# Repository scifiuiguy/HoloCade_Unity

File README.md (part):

# HoloCade for Unity

**HoloCade SDK** - A comprehensive SDK for developing VR/AR Location-Based Entertainment experiences in Unity with support for AI facial animation, large hydraulic haptics, and embedded systems integration.

<details>
<summary><strong>⚠️Author Disclaimer:</strong></summary>

<blockquote>
This is a brand new plugin as of November 2025. Parts of it are not fully fleshed out. The author built location-based entertainment activations for Fortune 10 brands over the past decade. This is the dream toolchain he wishes we had back then, but it probably still contains unforeseen bugs in its current form. V1.0 is considered Alpha. If you're seeing this message, it's because HoloCade has yet to deploy on a single professional project. Please use this code at your own risk. Also, this plugin provides code that may or may not run on systems your local and state officials may classify as  "amusement rides" or "theme park rides" which may fall under ASTM standards or other local regulations. HoloCade's author disclaims any liability for safety of guests or patrons or regulatory readiness. Please review the local regulations in your area prior to executing this code in any public venue. You are responsible for compliance in your state.
</blockquote>

</details><br>

> **🔗 Unreal Version:** Also available at [github.com/scifiuiguy/holocade_unreal](https://github.com/scifiuiguy/holocade_unreal)

---

## 📖 Overview

HoloCade is a comprehensive SDK for developing VR and AR Location-Based Entertainment (LBE) experiences. This repository **is** the **Unity 6 LTS** HoloCade package (`package.json` at the root), intended for use inside Unity projects via Package Manager or by embedding under `Packages/com.ajcampbell.holocade/`.

The HoloCade SDK democratizes LBE development by providing:
- **Experience Genre Templates** - Drag-and-drop complete LBE solutions
- **Low-Level APIs** - Technical modules for custom integration between game engine and various physical systems
- **AI-Driven Facial Animation** for immersive theater live actors (automated w/ NVIDIA ACE)
- **Wireless Trigger Controls** - Embedded buttons in costume/clothing for narrative state machine control through WiFi/Bluetooth
- **Large-Scale Hydraulic Haptics** for lift/motion platforms
- **Embedded Systems Integration** for costume-/prop-/wall-/furniture-mounted interfaces
- **Embedded Sensors** temperature, motion, face, and body tracking sensors to trigger escape room actions
- **Co-located XR Multiplayer LAN Experiences** with Unity NetCode for GameObjects
- **HMD and Hand Tracking** via OpenXR (Unity's native XR system)
- **6DOF Tracking** with SteamVR trackers and future extensibility

<details>
<summary><strong>⚠️OpenXR Note:</strong></summary>

<blockquote>
HoloCade uses **OpenXR exclusively** for all HMD and hand tracking access through Unity's native XR system (`XRHandSubsystem`, `InputDevices`). If OpenXR is not desired for your LBE deployment for any reason, but you still want to use an HoloCade experience genre template to get started, there may be some customization necessary in `HoloCadeHandGestureRecognizer` and in some of the Experience classes. Anywhere OpenXR is referenced, you may need to create an alternative version of that class with your SDK of choice replacing OpenXR usage.

</blockquote>

</details><br>

---

## 💭 Philosophy

<details>
<summary><strong>Why HoloCade?</strong></summary>

<blockquote>

Home console VR usage is nascent and difficult despite being steadily on the rise:
* 80 million monthly active users in the U.S. in 2025
* up 60% from 2020
* 10% of Americans started using VR regularly so far this decade

If that growth holds, we might reach 100 million regular VR users by end-of-decade, more than 1/4 of the population. It's not smartphone-era growth, but it's steady.

BUT...

Content budgets are skin-and-bone. 

Building for VR requires specialty talent compared to film/TV/gaming, and every dollar spent goes half as far due to...
* deeper fidelity challenges
* bigger QA hurdles
* evil perf op constraints

VR devs need a leg up. The industry has been in a funding desert since the Pandemic. "VR is all hype" rumors put the dev community on a respirator, and we never got off the ropes.

I get where investors are coming from. We're 10 years into modern VR. They need proof of ROI. We need to deliver in the black. We need better tools. We were building cars without factories.

A better analogy - Movie Theaters:
If a Hollywood studio invested millions on a new film before the streaming era, they'd be sunk if there were no 35mm projector and no movie theaters hungry to roll the next hit.

An even better analogy - the JAMMA Arcade Spec:
In 1985, the arcade industry was in a slump. All the arcade boxes were proprietary. Venues had to buy a new arcade box for every game. Devs had to design a whole arcade box for just THEIR game. Enter the JAMMA Spec. Suddenly venues could leave the same box in place and swap a card, and suddenly it's a new game! Same hardware, fresh regular content. Devs could focus on the game knowing reliable hardware was already on-site.

We need that for the VR industry:
* Devs need to be able to focus on dev, not hardware
* Venues need standard hardware so devs can bring them regular new content.

We have an chicken-egg situation. A standard spec for VR LBE is what we need.

Enter HoloCade. Free, open-source, plug-n-play across multiple genres.

</blockquote>

</details>

<details>
<summary><strong>Who is HoloCade for?</strong></summary>

<blockquote>

HoloCade is for professional teams building commercial Location-Based Entertainment installations. It's a professional-grade toolchain designed for teams of programmers and technical artists.

**Target audiences:**
- **Theme park attraction designers/engineers/production staff** - Building immersive attractions with motion platforms, embedded systems, and live actor integration
- **VR Arcade venue designers/engineers/production staff** - Deploying multiplayer VR experiences with synchronized motion and professional audio/lighting
- **Brands at trade shows** interested in wowing audiences with VR
- **3rd-party VR developers** who want to deploy new content rapidly to theme parks and VR Arcades
- **VR educators** who want to expose students to professional toolchains used in commercial LBE production

The SDK provides:
- ✅ **C# programmers** with robust APIs and extensible architecture
- ✅ **Unity developers** with drag-and-drop components and visual scripting
- ✅ **Content teams** with rapid deployment capabilities
- ✅ **Commercial projects** with free-to-use, MIT-licensed code

</blockquote>

</details>

<details>
<summary><strong>Who is HoloCade not for?</strong></summary>

<blockquote>

Developers with little or no experience with C# may struggle to put HoloCade to its fullest use. It is meant for a scale of production that would be challenging for lone developers. However, it can be a great learning tool for educators to prepare students to work on professional team projects.

**Important notes:**
- HoloCade is **not** a no-code solution. It requires programming knowledge (C# or Unity scripting) to customize experiences beyond the provided templates.
- HoloCade is designed for **team-based production** with multiple developers, technical artists, and production staff.
- HoloCade provides prefabs, but it assumes tech art team members have access to C# programmers on the team to back them up for customization.

</blockquote>

</details>

---

## 🎯 Quick Start

```csharp
using HoloCade.ExperienceTemplates;

// Create a moving platform experience
var platform = gameObject.AddComponent<MovingPlatformExperience>();
platform.InitializeExperience();

// Send normalized motion (hardware-agnostic)
platform.SendPlatformTilt(0.5f, -0.3f, 0f, 1.5f);  // TiltX, TiltY, Vertical, Duration
```

---

## 📚 Table of Contents

<details>
<summary><strong>THIS README</strong></summary>

<blockquote>

- [Prerequisites & Package Dependencies](#-prerequisites--package-dependencies)
- [Three-Tier Architecture](#-three-tier-architecture)
- [Hardware-Agnostic Input System](#-hardware-agnostic-input-system)
- [Features](#-features)
- [Experience Genre Templates](#experience-genre-templates-pre-configured-solutions)
- [Low-Level APIs](#low-level-apis-technical-modules)
- [Installation](#-installation)
- [Examples](#-examples)
- [Dedicated Server & Server Manager](#-dedicated-server--server-manager)
- [Roadmap](#-roadmap)
- [License](#-license)

</blockquote>

</details>

<details>
<summary><strong>OTHER READMEs IN THIS PROJECT</strong></summary>

<blockquote>

**Low-Level APIs:**
- [VRPlayerTransport README](https://github.com/scifiuiguy/holocade_unity/blob/main/Runtime/Core/VRPlayerTransport/README.md) - `Runtime/Core/VRPlayerTransport/README.md`
- [Input README](https://github.com/scifiuiguy/holocade_unity/blob/main/Runtime/Core/Input/README.md) - `Runtime/Core/Input/README.md`
- [VOIP README](https://github.com/scifiuiguy/holocade_unity/blob/main/Runtime/VOIP/README.md) - `Runtime/VOIP/README.md`
- [EmbeddedSystems README](https://github.com/scifiuiguy/holocade_unity/blob/main/Runtime/EmbeddedSystems/README.md) - `Runtime/EmbeddedSystems/README.md`
- [Cube Module README](https://github.com/scifiuiguy/holocade_unity/blob/main/Runtime/Cube/CUBE_MODULE_README.md) - `Runtime/Cube/CUBE_MODULE_README.md`
- [Cabinet NEXT_STEPS](https://github.com/scifiuiguy/holocade_unity/blob/main/Runtime/Cabinet/NEXT_STEPS.md) - `Runtime/Cabinet/NEXT_STEPS.md`

**Firmware Examples:**
- [FirmwareExamples README](https://github.com/scifiuiguy/holocade_unity/blob/main/FirmwareExamples/README.md) - `FirmwareExamples/README.md`
- [GunshipExperience README](https://github.com/scifiuiguy/holocade_unity/blob/main/FirmwareExamples/GunshipExperience/README.md) - `FirmwareExamples/GunshipExperience/README.md`
- [FlightSimExperience README](https://github.com/scifiuiguy/holocade_unity/blob/main/FirmwareExamples/FlightSimExperience/README.md) - `FirmwareExamples/FlightSimExperience/README.md`
- [EscapeRoom README](https://github.com/scifiuiguy/holocade_unity/blob/main/FirmwareExamples/EscapeRoom/README.md) - `FirmwareExamples/EscapeRoom/README.md`
- [Base Examples README](https://github.com/scifiuiguy/holocade_unity/blob/main/FirmwareExamples/Base/Examples/README.md) - `FirmwareExamples/Base/Examples/README.md`
- [Base Templates README](https://github.com/scifiuiguy/holocade_unity/blob/main/FirmwareExamples/Base/Templates/README.md) - `FirmwareExamples/Base/Templates/README.md`

</blockquote>

</details>

---

## 📦 Prerequisites & Package Dependencies

> **📦 HoloCade is a Unity Package** - See the [Installation](#-installation) section below for detailed setup instructions.

<details>
<summary><strong>Unity Version Requirements</strong></summary>

<blockquote>

- **Unity 6 LTS (Recommended)** or Unity 2022.3 LTS (Minimum)
- **Windows 10/11** (Primary platform)
- **Linux** (Experimental support)

</blockquote>

</details>

<details>
<summary><strong>HoloCade Package Dependencies</strong></summary>

<blockquote>

HoloCade requires several Unity packages. These are **automatically installed** when you install HoloCade via Package Manager or Git URL. If installing manually, install these via **Window > Package Manager**:

#### **Core Dependencies (Required)**

| Package | Version | Purpose | Installation |
|---------|---------|---------|--------------|
| **XR Plugin Management** | 4.4.0+ | VR/AR runtime management | `com.unity.xr.management` |
| **OpenXR Plugin** | 1.9.0+ | Cross-platform VR support (required for HMD and hand tracking) | `com.unity.xr.openxr` |
| **XR Hands** | 1.3.0+ | Hand tracking support (required for gesture recognition) | `com.unity.xr.hands` |
| **Input System** | 1.7.0+ | Modern input handling | `com.unity.inputsystem` |
| **uGUI (Unity UI + TextMeshPro)** | 2.0.0+ | UI framework + TextMeshPro for `OmniTextElement` and other in-cube text rendering. On Unity 6 LTS, `com.unity.ugui` includes the TMP runtime; legacy projects can use `com.unity.textmeshpro` 3.0.6+ instead. | `com.unity.ugui` |

> **⚠️ OpenXR Requirement:** HoloCade uses OpenXR exclusively for all HMD and hand tracking. Your HMD must support OpenXR (most modern VR headsets do, including Meta Quest, Windows Mixed Reality, and SteamVR-compatible headsets via OpenXR). If your deployment requires a different XR SDK, you will need to customize the HMD/hand tracking components. See the main Overview section for details.

#### **Multiplayer Dependencies (Required for AIFacemask)**

| Package | Version | Purpose | Installation |
|---------|---------|---------|--------------|
| **NetCode for GameObjects** | 1.8.0+ | Multiplayer networking | `com.unity.netcode.gameobjects` |
| **Unity Transport** | 2.2.0+ | Network transport layer | `com.unity.transport` |

#### **Optional Packages (Platform-Specific)**

| Package | Version | Purpose | When Needed |
|---------|---------|---------|-------------|
| **SteamVR Plugin** | 2.7.3+ | SteamVR integration (optional, for 6DOF body/prop tracking with SteamVR trackers) | If using SteamVR trackers for body/prop tracking |
| **Oculus Integration** | Latest | Meta Quest integration (optional, OpenXR handles Quest via OpenXR) | Only if you need Oculus-specific features beyond OpenXR |
| **XR Interaction Toolkit** | 2.5.0+ | VR interaction helpers | For advanced VR interactions |

</blockquote>

</details>

<details>
<summary><strong>Quick Setup (If You Cloned This Repo)</strong></summary>

<blockquote>

This repository **is the HoloCade package** (`package.json` at the repo root): there is no Unity host project here (no `Assets/` / `ProjectSettings/` in this clone).

**To use HoloCade in your own Unity project:**

1. Add it via **Package Manager → Add package from Git URL** (see [Installation](#-installation)), **or**
2. Clone or submodule this repo into `YourProject/Packages/com.ajcampbell.holocade/` (see embed options in [Installation](#-installation)).

Dependencies resolve from HoloCade’s `package.json` when the package is added to a project.

**Project window / tooling:** Optional shell and batch scripts (compile checks, dedicated-server launcher, version bump) live in **`BuildTooling~/`**. Folders whose names end with **`~`** are ignored by Unity’s Asset Database, so those files do not import into the Project window and do not log importer errors. This root **`README.md`** stays at the package root so it remains visible alongside `package.json` and imports as a normal text asset.

For installation options and Git URLs, see the [Installation](#-installation) section below.

</blockquote>

</details>

<details>
<summary><strong>Project Settings Configuration</strong></summary>

<blockquote>

After installing packages, configure:

1. **XR Plugin Management**
   - **Edit > Project Settings > XR Plug-in Management**
   - Enable **OpenXR** for your target platform (required for HMD and hand tracking)
   - Configure **OpenXR Feature Sets** (hand tracking, controllers, etc.)
   - **Note:** HoloCade uses OpenXR exclusively. Ensure hand tracking is enabled in OpenXR settings for gesture recognition to work.

2. **Input System**
   - **Edit > Project Settings > Player > Active Input Handling**
   - Select **"Both"** (supports old and new input systems)

3. **Physics**
   - **Edit > Project Settings > Physics**
   - Verify collision layers for VR interactions

</blockquote>

</details>

<details>
<summary><strong>Verification</strong></summary>

<blockquote>

To verify all dependencies are installed:

1. Open **Window > Package Manager**
2. Switch to **"In Project"** view
3. Confirm all required packages are listed

If you see compilation errors about missing namespaces:
- `Unity.Netcode` → Install NetCode for GameObjects
- `Unity.XR.OpenXR` → Install OpenXR Plugin
- `UnityEngine.InputSystem` → Install Input System

</blockquote>

</details>

<details>
<summary><strong>Common Issues & Troubleshooting</strong></summary>

<blockquote>

#### **"The type or namespace name 'NetworkBehaviour' could not be found"**
**Solution:** Install `com.unity.netcode.gameobjects` via Package Manager.

#### **"The type or namespace name 'InputSystem' could not be found"**
**Solution:** 
1. Install `com.unity.inputsystem`
2. Go to **Edit > Project Settings > Player**
3. Change **Active Input Handling** to **"Both"** or **"Input System Package (New)"**

#### **"Assembly has reference to non-existent assembly 'Unity.XR.OpenXR'"**
**Solution:** Install `com.unity.xr.openxr` and enable OpenXR in **Edit > Project Settings > XR Plug-in Management**.

#### **Package installation fails or gets stuck**
**Solution:**
1. Close Unity Editor
2. Delete `Library/` folder in project root
3. Delete `Packages/packages-lock.json`
4. Reopen Unity Editor (will reimport all packages)

#### **"Could not load file or assembly 'Unity.Netcode.Runtime'"**
**Solution:** 
1. Restart Unity Editor
2. If that fails, reimport NetCode package: **Package Manager > NetCode for GameObjects > Right-click > Reimport**

</blockquote>

</details>

---

## 🏗️ Three-Tier Architecture

HoloCade uses a modular three-tier architecture for code organization and server/client deployment.

### Code and Class Structure

<details>
<summary><strong>Tier 1: Low-Level APIs (Technical Modules)</strong></summary>

<blockquote>

Foundation modules providing core functionality:
- `HoloCadeCore` - VR/XR tracking abstraction, networking
- `HoloCadeAI` - Low-level AI API (LLM, ASR, TTS, container management)
- `LargeHaptics` - Platform/gyroscope control
- `EmbeddedSystems` - Microcontroller integration
- `ProAudio` - Professional audio console control via OSC
- `ProLighting` - DMX lighting control (Art-Net, USB DMX)
- `Retail` - Cashless tap card payment interface for VR tap-to-play
- `VOIP` - Low-latency voice communication with 3D HRTF spatialization
- `RF433MHz` - 433MHz wireless remote/receiver integration with rolling code validation

**Use these when:** Building custom experiences from scratch with full control.

</blockquote>

</details>

<details>
<summary><strong>Tier 2: Experience Genre Templates (Pre-Configured MonoBehaviours)</strong></summary>

<blockquote>

Ready-to-use complete experiences combining multiple APIs:
- `AIFacemaskExperience` - Live actor-driven multiplayer VR with wireless trigger buttons controlling automated AI facemask performances
- `MovingPlatformExperience` - A 4-gang hydraulic platform on which a single VR player stands while hooked to a suspended cable harness to prevent falling
- `GunshipExperience` - 4-player seated platform with 4DOF hydraulic motion driven by a 4-gang actuator platform with a player strapped in at each corner, all fixed to a hydraulic lift that can dangle players a few feet in the air
- `CarSimExperience` - A racing/driving simulator where 1-4 player seats are bolted on top of a 4-gang hydraulic platform
- `FlightSimExperience` - A single player flight sim with HOTAS controls in a 2-axis gyroscopic cockpit built with servo motors for pitch and roll. **⚠️ Requires outside-in tracking with cockpit-mounted trackers for Space Reset feature (see FlightSimExperience/README.md)** 
- `EscapeRoomExperience` - Puzzle-based escape room with embedded door lock/prop latch solenoids, sensors, and pro AV integration for light/sound and live improv actors
- `GoKartExperience` - Electric go-karts, bumper cars, race boats, or bumper boats augmented by passthrough VR or AR headsets enabling overlaid virtual weapons and pickups that affect the performance of the vehicles
- `SuperheroFlightExperience` - A dual-hoist-harness-and-truss system that lifts a player into the air and turns them prone to create the feeling of superhero flight as they punch fists out forward, up, or down

**Use these when:** Rapid deployment of standard LBE genres.

</blockquote>

</details>

<details>
<summary><strong>Tier 3: Your Custom Game Logic</strong></summary>

<blockquote>

Build your specific experience (Tier 3) on top of templates (Tier 2) or APIs (Tier 1).

</blockquote>

</details>

<details>
<summary><strong>When to Use What?</strong></summary>

<blockquote>

| Scenario | Use This | Why |
|----------|----------|-----|
| Building a gunship VR arcade game | `GunshipExperience` | Pre-configured for 4 players, all hardware setup included |
| Building a racing game | `CarSimExperience` | Simplified driving API, optimized motion profiles |
| Building a space combat game | `FlightSimExperience` | HOTAS integration ready, continuous rotation supported |
| Custom 3-player standing platform | Low-Level APIs | Need custom configuration not covered by templates |
| Live actor-driven escape room | `AIFacemaskExperience` | Wireless trigger buttons in costume control narrative state machine, automated AI facemask performances |
| Puzzle-based escape room | `EscapeRoomExperience` | Narrative state machine, door locks, prop sensors, embedded systems |
| Go-kart racing with VR/AR overlay | `GoKartExperience` | Passthrough VR/AR support, virtual weapons, item pickups, projectile combat |
| Superhero flight simulation | `SuperheroFlightExperience` | Dual-winch suspended harness, gesture-based control, free-body flight |
| Unique hardware configuration | Low-Level APIs | Full control over all actuators and systems |

**Rule of thumb:** Start with templates, drop to APIs only when you need customization beyond what templates offer.

</blockquote>

</details>

### LAN Server/Client Configuration

<details>
<summary><strong>Local Command Console</strong></summary>

<blockquote>

```
┌─────────────────────────────────────────────┐
│  Single PC (Command Console + Server)       │
│  ────────────────────────────────────────   │
│  • Command Console UI (monitoring)          │
│  • Server Manager (dedicated server)        │
│  • NVIDIA ACE Pipeline (if AIFacemask)       │
└───────────────────┬─────────────────────────┘
                    │
                    │ UDP Broadcast (port 7778)
                    │
        ┌───────────┴───────────┐
        │                       │
        ▼                       ▼
   ┌─────────┐            ┌─────────┐
   │  HMD 1  │            │  HMD 2  │
   │(Client) │            │(Client) │
   └─────────┘            └─────────┘
   ... (Player 1...N, Live Actor 1...N)
```

**Use when:** Simple setup, single machine, lightweight network traffic.

</blockquote>

</details>

<details>
<summary><strong>Dedicated Server + Separate Local Command Console</strong></summary>

<blockquote>

```
┌─────────────────────────────────────────────┐
│  Server PC (Dedicated Server)               │
│  ────────────────────────────────────────   │
│  • Server Manager (dedicated server)        │
│  • NVIDIA ACE Pipeline (if AIFacemask)      │
└───────────────────┬─────────────────────────┘
                    │
                    │ UDP Broadcast (port 7778)
                    │
        ┌───────────┴───────────┐
        │                       │
        ▼                       ▼
   ┌─────────┐            ┌─────────┐
   │  HMD 1  │            │  HMD 2  │
   │(Client) │            │(Client) │
   └─────────┘            └─────────┘
   ... (Player 1...N, Live Actor 1...N)

┌─────────────────────────────────────────────┐
│  Console PC (Command Console)               │
│  ────────────────────────────────────────   │
│  • Command Console UI (monitoring)           │
│  • Connected via UDP (port 7779)             │
└─────────────────────────────────────────────┘
```

**Use when:** Heavy processing workloads, better performance isolation, HMD battery life optimization.

</blockquote>

</details>

<details>
<summary><strong>Dedicated Server + Remote Command Console</strong></summary>

<blockquote>

```
┌─────────────────────────────────────────────┐
│  Server PC (Dedicated Server)               │
│  ────────────────────────────────────────   │
│  • Server Manager (dedicated server)        │
│  • NVIDIA ACE Pipeline (if AIFacemask)    │
└───────────────────┬─────────────────────────┘
                    │
                    │ UDP Broadcast (port 7778)
                    │
        ┌───────────┴───────────┐
        │                       │
        ▼                       ▼
   ┌─────────┐            ┌─────────┐
   │  HMD 1  │            │  HMD 2  │
   │(Client) │            │(Client) │
   └─────────┘            └─────────┘
   ... (Player 1...N, Live Actor 1...N)

                    │
                    │ Internet Node
                    │
                    ▼
┌─────────────────────────────────────────────┐
│  Remote Console PC (Command Console)       │
│  ────────────────────────────────────────   │
│  • Command Console UI (monitoring)          │
│  • Connected via UDP (port 7779) over       │
│    internet (VPN recommended)               │
└─────────────────────────────────────────────┘
```

**Use when:** Off-site monitoring (debugging/testing only - use VPN and authentication for security).

</blockquote>

</details>

<details>
<summary><strong>When to Use What Configuration?</strong></summary>

<blockquote>

| Scenario | Recommended Configuration | Why |
|----------|---------------------------|-----|
| Basic single-player experience | **Local Command Console** (same PC as server) | Simple setup, no need for separate machines. Command Console launches and manages server locally. |
| Basic multiplayer with RPCs but no heavy data transferring wirelessly | **Local Command Console** (same PC as server) | Network traffic is lightweight (player positions, events). Local Command Console can manage server on same machine efficiently. |
| Lots of heavy graphics processing you want to offload from VR HMD(s) | **Dedicated + Separate Local** or **Dedicated + Remote** | Offload GPU-intensive rendering and AI processing to dedicated server PC. Better performance isolation and HMD battery life. |
| Need to monitor the experience in real-time from off-site? | **Dedicated + Remote** ⚠️ | Remote Command Console can connect over network to monitor server status, player count, experience state, and logs from a separate location. **⚠️ Recommended for debugging/testing only. For general public operation, full internet isolation is recommended for security.** Requires authentication enabled in Command Protocol settings. |

**Configuration Options:**
- **Local Command Console:** Command Console (UI Panel) and Server Manager (dedicated server) run on the same PC. Simple setup, one machine.
- **Dedicated + Separate Local:** Server Manager runs on dedicated PC, Command Console runs on separate local PC (same LAN). Networked via UDP (port 7779). Better for heavy processing workloads.
- **Dedicated + Remote:** Server Manager runs on dedicated PC, Command Console runs on remote PC (over internet). Networked via UDP (port 7779). VPN and authentication recommended.

</blockquote>

</details>

---

## 🏗️ Standard Pop-up Layout

> **Note:** The Standard Pop-up Layout is **recommended but not required**. HoloCade can be deployed in any configuration that meets your needs. This standard format is optimized for rapid pop-up deployments in public venues.

HoloCade is applicable to a large variety of venues, but it is designed in particular to enable rapid deployment of pop-up VR LBE. The SDK pairs well with a standard physical layout which, when used, gives everyone in the ecosystem confidence of rapid deployment and content refresh.

<details>
<summary><strong>Overview</strong></summary>

<blockquote>

HoloCade is designed for **1-to-4 player co-located VR multiplayer experiences** in publicly accessible venues such as:
- Trade shows
- Civic centers
- Shopping malls
- Theme parks
- Corporate events
- Brand activations

#### Open Layout

- Standard minimum roomscale dimensions suitable for AIFacemask narratives and escape rooms
- Minimum 10' × 10' cordoned-off play space
- Virtual guardian setup recommended with 2-foot padding buffer to the cord to prevent player from striking outside viewer
- Consider outer margin buffer with secondary cord for extra safety (12' × 12')
- 20' × 20' recommended for any open layout using large haptics

#### Closed Layout

- 20' × 40' minimum play space to accommodate swinging ingress/egress walls
- Establish guardian with 2-foot padding buffer to walls for safety
- Consider safety cord to prevent players from reaching the Ops console

</blockquote>

</details>

<details>
<summary><strong>Space Recommendations</strong></summary>
<blockquote>

- **Play Area:** 100+ square feet of open play space
- **Ceiling Height:** Sufficient clearance for players swinging long padded props (minimum 10+ feet recommended)
- **Minimum Total Space:** 50% of total space may be allocated for retail, ingress, and egress infrastructure
- **Flexible Boundaries:** Play space can be cordoned off with temporary trade-show walls or dividers around the 50% play area

</blockquote>

</details>

<details>
<summary><strong>Minimum Square Footage</strong></summary>

<blockquote>

**Standard pop-up installation minimum square footage recommendation: ~40' × ~40'**

This includes:
- **Dual ingress/egress stations** (~12' × ~12' each) equipped with up to 4 VR HMDs apiece
- **Dual battery charging stations** ready for hot-swap after each playthrough
- **Charger stalls in staging area** near Ops Tech monitor console/server (~12' × ~12')
- **Play space** with enough room for ingress/egress door swing (~18' × ~40')
- **Lobby/Greeting area** with dual ingress/egress entry/exit (~10' × ~40')

</blockquote>

</details>

<details>
<summary><strong>Author's Framing Recommendations</strong></summary>

<blockquote>

<table>
<tr>
<td width="30%">

The author of HoloCade is a hobbyist TIG welder who has built many aluminum chassis frames. You can use the provided HoloCade OnShape procedural templates to quickly generate framing designs at dimensions you prefer, but HoloCade's author recommends you consider the following:

- **HoloCade's author is not a certified mechanical engineer** (he's a software engineer)
  - Author disclaims any liability in regard to use of any included CAD designs
  - Included designs are only a starting point
- **Minimum 1" square tube**
  - Mild steel - best price
  - Stainless steel - best strength and good corrosion resistance (most premium)
  - 5051 aluminum w/ clear coat - best balance of strength, weldability, corrosion resistance, and price
- **Use stainless steel hardware** for minimum galvanic corrosion
  - HoloCade CAD templates default to rivnut joints configuration for rapid assembly/teardown
  - HoloCade CAD templates contain teardown animation rigs
    - Too many welds = hard to box and ship
    - Too many bolts = time lost during assembly/teardown
    - OnShape teardown animation rigs aim to provide a Goldilocks balance between the two
  - Male/female rivnut pair config with flanged 1/4-20 Imperial or M6x1.0 Metric hex recommended
    - Pairing rivnuts opens option to run a bolt through one frame piece or the other or both
  - Rivnuts yield fastest assembly teardown with only 1 impact gun & 1 Imperial bit/1 Metric bit
  - Rivnuts avoid need for washers, nuts, and other loose parts - 1 bolt per rivnut - nothing more
  - **OPTIONAL:** eliminate loose bolts
    - Cut an access port ortho to each bolt hole (opposite side of display face)
    - Install double-capture nuts inside tube w/ an amount of play equal to drill depth
    - Bolts become semi-permanently attached to the frame - no more loose parts
  - Choose bolt shank length at 1.5X tube width e.g. 2 1" square tubes join flush w/ 1 1.5" flanged hex bolt
  - **NOTE:** rivnut collar mates w/ a .375" or 10mm hole but opposing bolt flange needs a 0.26" or 6.6mm hole
- **Minimum 0.625" wall thickness**
  - Widely available and perfectly reliable @ 10ft high with no heavy loads on top
  - Hire a qualified engineer to confirm loaded designs (marquees, jumbotrons, etc.)
- **Minimum 6" wall depth**
  - 1" tube x2 inner/outer
  - 1" tube x2 inner/outer pocket door guide
  - 2" pocket door
- **Weld type recommendation** in order of high-to-low quality-for-price:
  - Laser
  - TIG
  - MIG
- **Welder should grind all welds clean** to ensure flush-mount at all joints
- **Ground welds are more likely to fail** - torture test random pieces for proper penetration
- **HoloCade OnShape CAD templates + hired welders** = MUCH cheaper than off-the-shelf branded solutions
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
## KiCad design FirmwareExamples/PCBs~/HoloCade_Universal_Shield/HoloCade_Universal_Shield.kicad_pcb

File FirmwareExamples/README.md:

# HoloCade Firmware Examples

**Firmware examples, templates, and documentation for HoloCade Embedded Systems integration.**

---

## 📁 Directory Structure

```
FirmwareExamples/
├── Base/                          # Generic examples and templates for all experiences
│   ├── Templates/                  # Reusable header templates
│   │   ├── HoloCade_Wireless_TX.h   # Wireless transmission template
│   │   ├── HoloCade_Wireless_RX.h   # Wireless reception template
│   │   ├── HoloCade_CAN.h           # CAN bus communication template
│   │   ├── ScissorLift_Controller.h  # Scissor lift control (CAN or GPIO)
│   │   └── ActuatorSystem_Controller.h  # Actuator system control
│   └── Examples/                   # Functionality-based examples
│       ├── ButtonMotor_Example.ino              # Main example (all platforms)
│       ├── ScissorLift_Controller.ino          # Scissor lift standalone
│       └── ActuatorSystem_Controller.ino       # Actuator system standalone
│
├── EscapeRoom/                     # Escape room specific examples
│   └── DoorLock/                   # Door lock control examples
│       └── DoorLock_Example.ino                 # Main example (all platforms)
│
└── GunshipExperience/              # Gunship experience specific examples
    ├── FourPlayerRig/               # Four-player scissor lift platform variant
    │   ├── GunshipExperience_ECU.ino   # Parent ECU for 4DOF motion platform (uses Universal Shield)
    │   ├── Gun_ECU.ino                  # Child ECU for per-station gun control
    │   └── README.md                    # Four-player rig firmware documentation
    └── SinglePlayerRig/            # Single-player custom chassis variant
        ├── GunshipExperience_ECU.ino   # Parent ECU for single-player motion platform (uses Driver Shield)
        ├── Gun_ECU.ino                  # Child ECU for gun control with servos
        └── README.md                    # Single-player rig firmware documentation
```

---

## 🎯 Quick Start

### **Using Templates**

1. **Copy template header** to your sketch directory:
   ```cpp
   // Copy from: FirmwareExamples/Base/Templates/HoloCade_Wireless_RX.h
   // To: YourSketch/HoloCade_Wireless_RX.h
   ```

2. **Include in your sketch**:
   ```cpp
   #include "HoloCade_Wireless_RX.h"
   
   void setup() {
     HoloCade_Wireless_Init("VR_Arcade_LAN", "password", 8888);
   }
   
   void loop() {
     HoloCade_ProcessIncoming();
   }
   ```

### **Using Examples**

1. **Choose your platform** (ESP32, ESP8266, Arduino+WiFi, etc.)
2. **Open the appropriate example**:
   - Use main example (`ButtonMotor_Example.ino` or `DoorLock_Example.ino`) for most platforms
   - Use ESP8266 variant if using ESP8266 (shows platform-specific pin config)
3. **Adjust GPIO pins** in Configuration section to match your hardware
4. **Configure WiFi credentials** and Unity PC IP address
5. **Upload to your microcontroller**

---

## 📚 Documentation

- **[Base/Templates/README.md](Base/Templates/README.md)** - Template usage guide
- **[Base/Examples/README.md](Base/Examples/README.md)** - Base example documentation
- **[EscapeRoom/README.md](EscapeRoom/README.md)** - Escape room examples guide
- **[GunshipExperience/README.md](GunshipExperience/README.md)** - Gunship experience examples guide
- **[GunshipExperience/Gunship_Hardware_Specs.md](GunshipExperience/Gunship_Hardware_Specs.md)** - Complete hardware specifications for gun solenoid kickers
- **[HoloCade_PCBs (KiCAD designs)](https://github.com/scifiuiguy/HoloCade_PCBs)** - Universal Shield, Child Shield, and Driver Shield PCBs (schematics, layouts, BOM, research). **Not** shipped inside this package; clone or browse that repository for board files.

---

## 🔧 Platform Support

All examples support multiple platforms. The main examples work on all platforms with minor GPIO pin adjustments.

| Platform | Wireless | Example File | Notes |
|----------|----------|--------------|-------|
| **ESP32** | ✅ Built-in | All examples | Full support, recommended |
| **ESP8266** | ✅ Built-in | All examples | Limited GPIO pins, adjust pin assignments |
| **ESP32-C3 (Pico-Click)** | ✅ Built-in | All examples | **v2.0:** Will replace ESP8266 as default for wireless buttons in clothing/props |
| **Arduino + WiFi Shield** | ✅ Via shield | All examples | Adjust GPIO pins, use shield library |
| **STM32 + WiFi Module** | ✅ Via module | All examples | Adjust GPIO pins, use module library |
| **Raspberry Pi** | ✅ Built-in | All examples | Adjust GPIO pins, use Linux sockets |
| **Jetson Nano** | ✅ Built-in | All examples | Adjust GPIO pins, use Linux sockets |

**Note:** All examples are platform-agnostic. Adjust GPIO pin assignments in the Configuration section to match your hardware. See comments in each example for platform-specific pin recommendations.

### **v2.0 Platform Migration: Pico-Click C3**

**Planned for v2.0:** The open-source [Pico-Click C3](https://github.com/pico-click) project (ESP32-C3 based) will be integrated as the default platform for hidden embedded wireless buttons in clothing and props, replacing the current ESP8266-based implementation.

**Advantages of ESP32-C3 over ESP8266:**
- **Performance:** 160 MHz RISC-V processor (vs. 80 MHz on ESP8266)
- **Connectivity:** Dual WiFi + Bluetooth 5.0 (vs. WiFi-only on ESP8266)
- **Power Efficiency:** 5 µA deep sleep (vs. 20 µA on ESP8266) - critical for battery-powered costume buttons
- **Memory:** 400 KB SRAM (vs. limited SRAM on ESP8266)
- **Form Factor:** Pico-Click C3 provides optimized form factor for embedding in clothing and props

Current ESP8266 examples will be migrated to Pico-Click C3 in v2.0. See main roadmap for details.

---

## 📝 Notes

### **FirmwareExamples Folder**

**Important:** The `FirmwareExamples/` folder is **not a special folder** in either engine. It's purely for **organization and documentation** of firmware examples and templates.

- ✅ **Safe to reorganize** - No engine dependencies
- ✅ **Safe to rename** - No code references
- ✅ **Documentation only** - Examples and templates for developers
- ✅ **Not included in builds** - Firmware files are not game engine assets

**Note:** We use `FirmwareExamples/` instead of `Resources/` to avoid Unity's special `Resources/` folder behavior (which includes all assets in builds). Firmware examples are not Unity assets and should not be included in game builds.

**Organization:** All embedded hardware firmware examples are located in `FirmwareExamples/`, organized by experience type. Game engine code references these examples in documentation but does not depend on their location.

---

## 🚀 Experience-Specific Examples

Examples are organized by experience type:

- **Base/** - Generic examples usable by any experience
  - `ScissorLift_Controller.ino` - Standalone scissor lift control (CAN bus or GPIO)
  - `ActuatorSystem_Controller.ino` - Standalone 4-actuator hydraulic control
  - `ButtonMotor_Example.ino` - Generic button & motor example
- **EscapeRoom/** - Escape room specific (door locks, props, sensors)
- **GunshipExperience/** - Gunship experience (parent ECU for 4DOF motion platform, child ECUs for per-station gun control)
- **AIFacemask/** - (Future) Live actor costume examples
- **MovingPlatform/** - (Future) Motion platform sensor examples

## 🔌 CAN Bus Support

The scissor lift controller supports **CAN bus communication** for manufacturer ECUs (e.g., Genie/Skyjack lifts):

- **CAN Bus Mode (default):** Sends joystick commands to manufacturer ECU via CAN bus
- **Direct GPIO Mode:** Direct motor control for custom builds or testing
- **Platform Support:** ESP32 (native TWAI), Arduino (MCP2515), STM32 (native), Linux (SocketCAN)

See `GunshipExperience/README.md` for CAN bus configuration instructions.

---

## 📄 License

MIT License - Copyright (c) 2025 AJ Campbell

---

**Built for HoloCade**

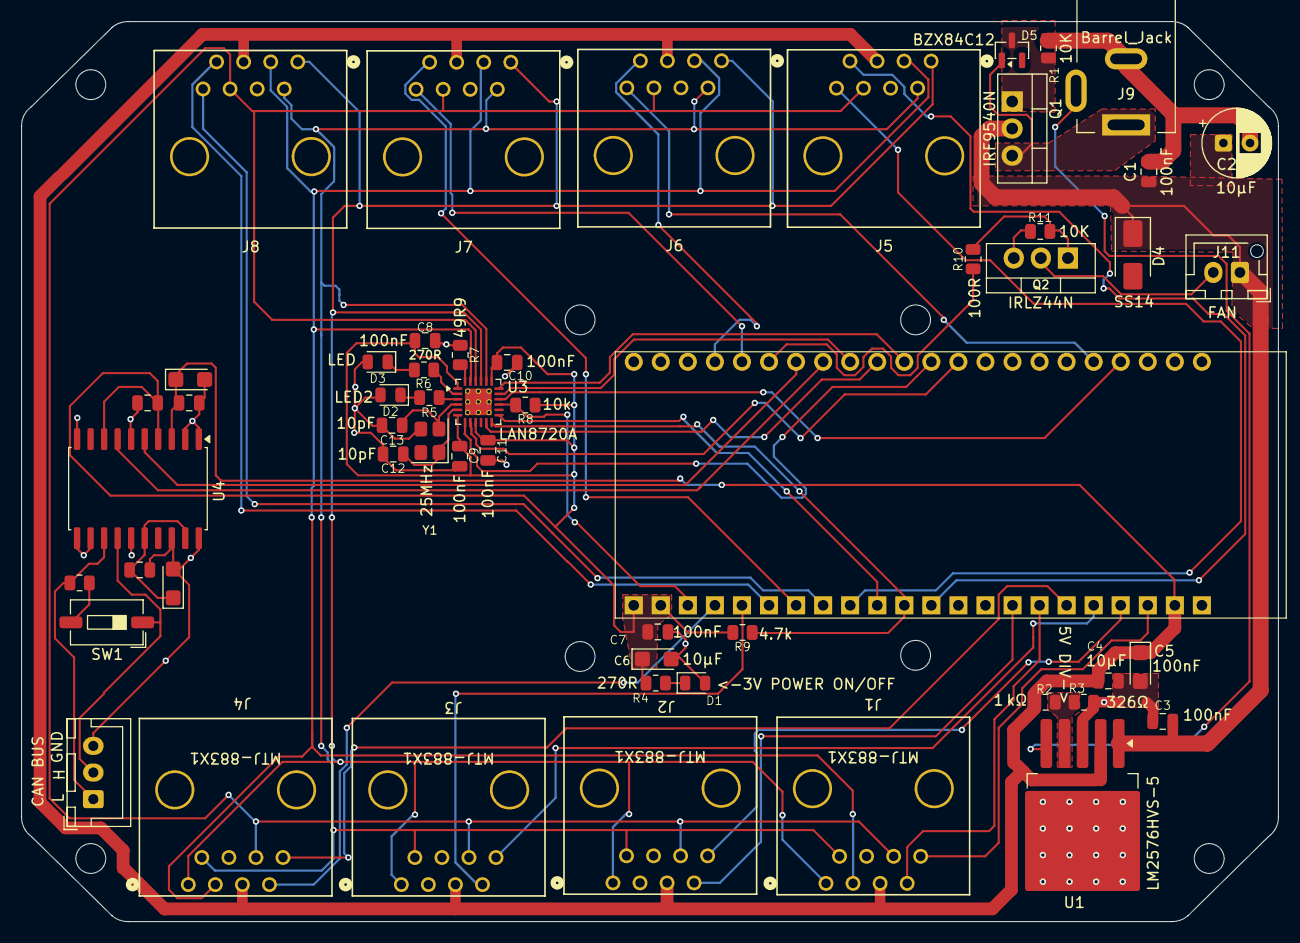
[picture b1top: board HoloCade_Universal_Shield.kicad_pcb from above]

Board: 2 copper layers, 118.0 x 84.5 mm, 54 parts (0 on the bottom side), 55 nets.

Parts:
C1, C3, C4, C7, C8, C9, C10, C11, C14, C15, C17: 100nF; C_0805_2012Metric
C2: 10µF; CP_Radial_D6.3mm_P2.50mm
C5, C6: 10µF; CP_EIA-3216-18_Kemet-A
C12, C13: 10pF; C_0805_2012Metric
C16, C18: 4.7µF; CP_EIA-3216-18_Kemet-A
D1, D2, D3: LED; LED_0805_2012Metric
D4: SS14; D_SMA
D5: BZX84C12; SOT-23
J1, J2, J3, J4, J5, J6, J7, J8: MTJ-883X1; CONN_MTJ-883X1_ADM
J9: Barrel_Jack; BarrelJack_Kycon_KLDX-0202-xC_Horizontal
J10: CAN BUS; JST_XH_B3B-XH-A_1x03_P2.50mm_Vertical
J11: FAN; JST_XH_B2B-XH-AM_1x02_P2.50mm_Vertical
Q1: IRF9540N; TO-220-3_Vertical
Q2: IRLZ44N; TO-220-3_Vertical
R1, R11: 10K; R_0805_2012Metric
R2: 1 kΩ; R_0805_2012Metric
R3: 326Ω; R_0805_2012Metric
R4, R5, R6: 270R; R_0805_2012Metric
R7: 49R9; R_0805_2012Metric
R8: 10k; R_0805_2012Metric
R9: 4.7k; R_0805_2012Metric
R10: 100R; R_0805_2012Metric
R12: 120R; R_0805_2012Metric
SW1: SW_DIP_x01; SW_DIP_SPSTx01_Slide_6.7x4.1mm_W6.73mm_P2.54mm_LowProfile_J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
U1: LM2576HVS-5; TO-263-5_TabPin3
U2: ESP32-S3-2x22; ESP32-S3_2x22_Header_v3
U3: LAN8720A; VQFN-24-1EP_4x4mm_P0.5mm_EP2.5x2.5mm_ThermalVias
U4: ADM3057ExRW; SOIC-20W_7.5x12.8mm_P1.27mm
Y1: 25MHz; Crystal_SMD_3225-4Pin_3.2x2.5mm

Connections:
+3.3V: C6.1, C7.1, C8.1, C9.1, C10.1, C11.1, C14.1, R4.1, R8.1, R9.1, U2.1 (VDD3P3), U2.2 (VDD3P3_2), U3.1 (VDD2A), U3.6 (VDDCR), U3.9 (VDDIO), U3.19 (VDD1A), U4.4 (VIO), U4.8 (STBY)
+5V: C4.1, C5.1, C15.1, C16.1, J1.5, J2.5, J3.5, J4.5, J5.5, J6.5, J7.5, J8.5, R2.2, U1.2 (OUT), U2.21 (VIN), U4.3 (VCC)
+24_12V: C1.1, C2.1, C3.2, D4.1 (K), J11.1, Q1.2 (D), U1.1 (VIN)
/FAN_SW: D4.2 (A), J11.2, Q2.2 (D)
/IO1: J6.7, U2.26 (GPIO1)
/IO2: J7.8, U2.27 (GPIO2)
/IO4: J4.7, U2.4 (GPIO4)
/IO5: J3.7, U2.5 (GPIO5)
/IO6: J8.7, U2.6 (GPIO6)
/IO7: J7.7, U2.7 (GPIO7)
/IO8: J5.7, U2.12 (GPIO8)
/IO9: J2.7, U2.15 (GPIO9)
/IO10: J1.7, U2.16 (GPIO10)
/IO11: J4.8, U2.17 (GPIO11)
/IO12: J3.8, U2.18 (GPIO12)
/IO13: J2.8, U2.19 (GPIO13)
/IO14: J1.8, U2.20 (GPIO14)
/IO15: J8.8, U2.8 (GPIO15)
/IO16: J5.8, U2.9 (GPIO16)
/IO17: U2.10 (GPIO17), U3.13 (MDC)
/IO18: R9.2, U2.11 (GPIO18), U3.12 (MDIO)
/IO20: U2.41 (GPIO20), U3.16 (TXEN)
/IO21: J6.8, U2.40 (GPIO21)
/IO35: U2.35 (GPIO35), U3.8 (RXD0/MODE0)
/IO36: U2.34 (GPIO36), U3.7 (RXD1/MODE1)
/IO37: U2.33 (GPIO37), U3.18 (TXD1)
/IO38: U2.32 (GPIO38), U3.11 (CRS_DV/MODE2)
/IO39: U2.31 (GPIO39), U3.17 (TXD0)
/IO40: U2.30 (GPIO40), U4.7 (TXD)
/IO41: U2.29 (GPIO41), U4.5 (RXD)
/IO42: R10.1, U2.28 (GPIO42)
/JACK_SW: J9.3, U1.5 (~ON/OFF)
/LED1: R5.1, U3.3 (LED1/REGOFF)
/LED2: R6.1, U3.2 (LED2/~INTSEL)
/RBIAS: R7.1, U3.24 (RBIAS)
/RESET_N: R8.2, U2.3 (EN), U3.15 (~RST)
/RX+: J1.3, J2.3, J3.3, J4.3, J5.3, J6.3, J7.3, J8.3, U3.23 (RXP)
/RX-: J1.6, J2.6, J3.6, J4.6, J5.6, J6.6, J7.6, J8.6, U3.22 (RXN)
/TX+: J1.1, J2.1, J3.1, J4.1, J5.1, J6.1, J7.1, J8.1, U3.21 (TXP)
/TX-: J1.2, J2.2, J3.2, J4.2, J5.2, J6.2, J7.2, J8.2, U3.20 (TXN)
GND: C1.2, C2.2, C3.1, C4.2, C5.2, C6.2, C7.2, C8.2, C9.2, C10.2, C11.2, C12.2, C13.2, C14.2, C15.2, C16.2, D1.2 (A), D2.2 (A), D3.2 (A), J1.4, J2.4, J3.4, J4.4, J5.4, J6.4, J7.4, J8.4, J9.2, Q2.3 (S), R1.2, R3.2, R7.2, R11.1, U1.3 (GND), U2.22 (GND), U2.23 (GND), U2.43 (GND), U2.44 (GND), U3.25 (VSS), U4.1 (GND1), U4.2 (GND1), U4.6 (SILENT), U4.10 (GND1), U4.11 (GND2), U4.12 (RS), U4.15 (GND2), Y1.3
unnamed: D1.1 (K), R4.2
unnamed: D2.1 (K), R5.2
unnamed: D3.1 (K), R6.2
unnamed: D5.1 (A), J9.1, Q1.3 (S)
unnamed: D5.3 (K), Q1.1 (G), R1.1
unnamed: J10.1, R12.1, U4.13 (CANL)
unnamed: J10.2, SW1.1, U4.14 (CANH)
unnamed: C17.2, C18.2, J10.3, U4.18 (GNDISO), U4.20 (GNDISO)
unnamed: Q2.1 (G), R10.2, R11.2
unnamed: R12.2, SW1.2
unnamed: R2.1, R3.1, U1.4 (FB)
unnamed: C12.1, U3.5 (XTAL1/CLKIN), Y1.1
unnamed: C13.1, U3.4 (XTAL2), Y1.2
unnamed: C17.1, C18.1, U4.16 (VISOIN), U4.19 (VISOOUT)

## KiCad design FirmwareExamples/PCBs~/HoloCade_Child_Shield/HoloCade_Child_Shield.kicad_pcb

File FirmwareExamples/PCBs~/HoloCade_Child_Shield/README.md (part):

# HoloCade Child Shield

**Also known as:** LBCS

## Overview

The Child Shield is a simplified derivative of the Universal Shield (HCUS). It keeps the same ESP32-S3 parent ECU pin map and Ethernet PHY but reduces the aux bus to **one** RJ45 port and drops CAN entirely. The goal is to provide a tiny, inexpensive parent/child hybrid board for installations that only need a single downstream device or a dedicated “mini HCUS” inside a prop or remote enclosure.

**Current design goals:**
- 1× RJ45 (Ethernet only). No CAN, no extra ADC/PWM breakouts.
- Powered either from the parent HCUS via the PoE/DIP/diode rail **or** from a local USB‑C Li‑ion pack (5 V input only).
- No onboard buck converter, reverse-polarity MOSFET, or fan header—the board expects regulated 5 V and relies on passive cooling.
- Keep the ESP32-S3 personality-adapter footprint for firmware parity with HCUS.
- Target the smallest possible PCB outline for costume props, handheld gadgets, and wireless sensor clusters.

> Until this document is fleshed out, refer to the [Universal Shield README](../HoloCade_Universal_Shield/README.md) for fully documented schematics, BOM, and power notes. The Child Shield uses that design as its baseline.

---

## Documentation Template (to be completed)

The sections below intentionally keep the same structure as the Universal Shield README. Each section contains a short note describing what still needs to be written for the Child Shield variant.

<details>
<summary><strong>Electronic Control Unit (ECU)</strong></summary>

<div style="margin-left: 20px;">
Provide a summarized ECU primer tailored to the Child Shield. Emphasize that this board is meant for ultra-lightweight, Ethernet-only nodes (wearables, handheld props, remote sensors) that either sip power from HCUS or carry their own USB‑C battery.
</div>

</details>

<details>
<summary><strong>Child Shield Role in the HCUS Ecosystem</strong></summary>

<div style="margin-left: 20px;">
Explain how the Child Shield can operate as:
- A “micro parent” when only one Ethernet child device is required.
- A pre-wired breakout that ships with finished props or costume pieces (power via USB‑C).
- A remote Ethernet-only repeater that backhauls data to a full HCUS when PoE is toggled on.
Document the rules for when to toggle PoE off (battery-powered mode) vs on (HCUS-powered mode), and reiterate that no CAN bus is present on this variant.
</div>

</details>

<details>
<summary><strong>Motivation / Modularity Advantage</strong></summary>

<div style="margin-left: 20px;">
Describe the cost/space savings of a single-port shield vs. an 8-port backplane. Document the target BOM (<$15 at scale) and the intended use cases (wearables, props, distributed IoT nodes).
</div>

</details>

<details>
<summary><strong>Key Features (Child Shield)</strong></summary>

<div style="margin-left: 20px;">
- 1× RJ45 aux port (Ethernet only; same pin map as AUX1 on HCUS)
- ESP32-S3 socket (same as Universal Shield) for firmware compatibility
- Power flexibility: accepts 5 V from HCUS PoE rail or from local USB‑C input
- No CAN transceiver, no LM2576 buck converter, no fan header
- Reduced board outline sized for small enclosures (exact dimensions TBD)
</div>

</details>

<details>
<summary><strong>High-Level Block Diagram</strong></summary>

<div style="margin-left: 20px;">
Add a simplified ASCII diagram once schematic capture begins. Use the Universal Shield diagram as a starting point, but replace the 8-port block with a single “Aux Port J1” call-out.
</div>

</details>

<details>
<summary><strong>Project Files</strong></summary>

<div style="margin-left: 20px;">
Planned filenames (to be created when schematic/PCB are captured):
- `HoloCade_Child_Shield.kicad_pro`
- `HoloCade_Child_Shield.kicad_sch`
- `HoloCade_Child_Shield.kicad_pcb`
- `HoloCade_Child_Shield.kicad_prl`
Note: Until those exist, the folder contains a working copy of the Universal Shield project as a springboard.
</div>

</details>

<details>
<summary><strong>Power Architecture</strong></summary>

<div style="margin-left: 20px;">
Document the simplified power path:
- 5 V PoE from HCUS → DIP switch → diode → RJ45 pin 4
- Optional USB‑C 5 V input (with reverse-current blocking so it doesn’t backfeed HCUS)
- ESP32-S3 VIN receives 5 V directly (no onboard buck). Note USB‑C current limit assumptions.
Clarify fuse strategy (likely deferred to parent HCUS) and diode usage.
</div>

</details>

<details>
<summary><strong>Component Set / BOM</strong></summary>

<div style="margin-left: 20px;">
Create a slimmed-down BOM once the schematic is finalized. Expected parts:
- ESP32-S3 headers + UART debug header
- LAN8720A PHY + 25 MHz crystal + magnetics
- Single RJ45 (MTJ-883X1 or similar)
- USB‑C connector (5 V only, no PD)
- DIP switch + Schottky diode for PoE gating
- Bypass caps, status LEDs, optional ESD protection
</div>

</details>

<details>
<summary><strong>Aux Port Pinout (Single-Port)</strong></summary>

<div style="margin-left: 20px;">
Reuse the T568B table from the Universal Shield but annotate that only J1 exists. Clarify how ADC/PWM mapping changes (likely reusing AUX1 nets).
</div>

</details>

<details>
<summary><strong>Enclosure / Mechanical Notes</strong></summary>

<div style="margin-left: 20px;">
- Planned enclosure: **Polycase TerraForm TF-1741TX** (ABS, tool-less lid) – [Product page](https://www.polycase.com/tf-1741tx). Fits a single RJ45, USB-C, and low-profile ESP32 module. Document mounting-hole pattern once the PCB outline is finalized.
- Add measurements for the smaller board, recommended potting volumes, and any mounting-hole changes once the layout exists. Capture whether standoffs align with the TF-1741TX bosses or require adhesive-backed posts.
</div>

</details>

<details>
<summary><strong>Future Work</strong></summary>

<div style="margin-left: 20px;">
- Finalize schematic/layout
- Generate dedicated 3D models and assembly drawings
- Produce a minimal BOM + fabrication notes
- Write firmware notes for "single-port parent" mode
- **TP4056 Battery Integration** - Integrate TP4056 USB-C lithium battery charging module directly onto the Child Shield PCB with exposed battery connection pads (B+/B-). Enables portable, battery-powered operation for wearable props, handheld gadgets, and remote sensor clusters. Includes power path management (USB-C charging + battery power), boost converter for 5V output (ESP32 dev board compatibility), and battery protection circuitry. See v2.0 roadmap for implementation details.
</div>

</details>

<details>
<summary><strong>High-Level Component Diagram</strong></summary>

<div style="margin-left: 20px;">

```
          ┌────────────────────────────────────────┐
          |                                        │
    ┌─────▲───────┐    ┌───────┐ +5V               │
    │ Barrel Jack │───→│LM2576 │────┐       ┌──────▼───────┐
    │  12V/24V    │    │ Buck  │    │       │ 12/24V Fan   │
    └─────────────┘    └───────┘    │       └───────┬──────┘
                           │+5V     │               ▼
                           │        │  ┌────────────────────────┐
                           │        └─→│         ESP32-S3       │
                           │           │      (Motherboard)     │
                           │           └──▲──────────────▲──────┘
                           │              │              │
                           │         ┌────▼────┐    ┌────▼────┐
                           │         │LAN8720A │    │ADM3057E │
                           │         │Ethernet │    │ CAN-FD  │
                           │         └────▲────┘    └────▲────┘
                           │              │              │
                           │              │         ┌────▼─────┐
                           │              │         │CAN 3-pin │
                           │              │         └──────────┘         
                    ┌──────▼──────────────▼──────────────────┐   
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
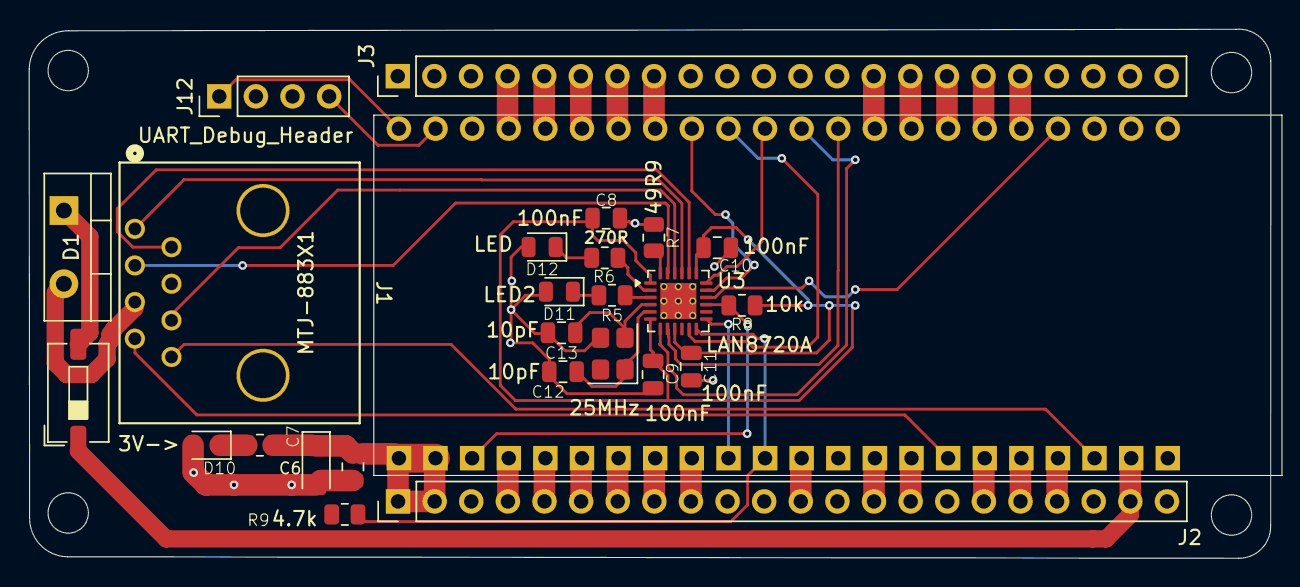
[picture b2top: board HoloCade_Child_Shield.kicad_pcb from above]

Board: 2 copper layers, 86.1 x 36.7 mm, 26 parts (0 on the bottom side), 51 nets.

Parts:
C6: 10µF; CP_EIA-3216-18_Kemet-A
C7, C8, C9, C10, C11: 100nF; C_0805_2012Metric
C12, C13: 10pF; C_0805_2012Metric
D1: MBR735; TO-220-2_Vertical
D10, D11, D12: LED; LED_0805_2012Metric
J1: MTJ-883X1; CONN_MTJ-883X1_ADM
J2, J3: Conn_01x22_Pin; PinHeader_1x22_P2.54mm_Vertical
J12: UART_Debug_Header; PinHeader_1x04_P2.54mm_Vertical
R4, R5, R6: 270R; R_0805_2012Metric
R7: 49R9; R_0805_2012Metric
R8: 10k; R_0805_2012Metric
R9: 4.7k; R_0805_2012Metric
SW2: J1_PWR_SW; SW_DIP_SPSTx01_Slide_6.7x4.1mm_W6.73mm_P2.54mm_LowProfile_J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
U2: ESP32-S3-2x22; ESP32-S3_2x22_Header_v3
U3: LAN8720A; VQFN-24-1EP_4x4mm_P0.5mm_EP2.5x2.5mm_ThermalVias
Y1: 25MHz; Crystal_SMD_3225-4Pin_3.2x2.5mm

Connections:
+3.3V: C6.1, C7.1, C8.1, C9.1, C10.1, C11.1, J2.1, J2.2, J12.2, R4.1, R8.1, R9.1, U2.1 (VDD3P3), U2.2 (VDD3P3_2), U3.1 (VDD2A), U3.6 (VDDCR), U3.9 (VDDIO), U3.19 (VDD1A)
+5V: J2.21, SW2.1, U2.21 (VIN)
/IO0: J3.14, U2.36 (GPIO0)
/IO1: J3.4, U2.26 (GPIO1)
/IO2: J3.5, U2.27 (GPIO2)
/IO4: J2.4, U2.4 (GPIO4)
/IO5: J2.5, U2.5 (GPIO5)
/IO6: J2.6, U2.6 (GPIO6)
/IO7: J2.7, U2.7 (GPIO7)
/IO8: J2.12, U2.12 (GPIO8)
/IO9: J2.15, U2.15 (GPIO9)
/IO10: J1.7, J2.16, U2.16 (GPIO10)
/IO11: J2.17, U2.17 (GPIO11)
/IO12: J2.18, U2.18 (GPIO12)
/IO13: J2.19, U2.19 (GPIO13)
/IO14: J1.8, J2.20, U2.20 (GPIO14)
/IO15: J2.8, U2.8 (GPIO15)
/IO16: J2.9, U2.9 (GPIO16)
/IO17: U2.10 (GPIO17), U3.13 (MDC)
/IO18: R9.2, U2.11 (GPIO18), U3.12 (MDIO)
/IO20: U2.41 (GPIO20), U3.16 (TXEN)
/IO21: J3.18, U2.40 (GPIO21)
/IO24: J12.4, U2.24 (U0TXD)
/IO35: U2.35 (GPIO35), U3.8 (RXD0/MODE0)
/IO36: U2.34 (GPIO36), U3.7 (RXD1/MODE1)
/IO37: U2.33 (GPIO37), U3.18 (TXD1)
/IO38: U2.32 (GPIO38), U3.11 (CRS_DV/MODE2)
/IO39: U2.31 (GPIO39), U3.17 (TXD0)
/IO40: J3.8, U2.30 (GPIO40)
/IO41: J3.7, U2.29 (GPIO41)
/IO42: J3.6, U2.28 (GPIO42)
/IO44: J12.3, U2.42 (U0RXD)
/IO45: J3.15, U2.37 (GPIO45)
/IO46: J2.14, J3.16, U2.14 (GPIO46), U2.38 (GPIO46)
/IO47: J3.17, U2.39 (GPIO47)
/LED1: R5.1, U3.3 (LED1/REGOFF)
/LED2: R6.1, U3.2 (LED2/~INTSEL)
/RBIAS: R7.1, U3.24 (RBIAS)
/RESET_N: R8.2, U2.3 (EN), U3.15 (~RST)
/RX+: J1.3, U3.23 (RXP)
/RX-: J1.6, U3.22 (RXN)
/TX+: J1.1, U3.21 (TXP)
/TX-: J1.2, U3.20 (TXN)
GND: C6.2, C7.2, C8.2, C9.2, C10.2, C11.2, C12.2, C13.2, D10.2 (A), D11.2 (A), D12.2 (A), J1.4, J2.22, J3.1, J3.21, J3.22, J12.1, R7.2, U2.22 (GND), U2.23 (GND), U2.43 (GND), U2.44 (GND), U3.25 (VSS), Y1.3
unnamed: D1.2 (A), J1.5
unnamed: D1.1 (K), SW2.2
unnamed: D10.1 (K), R4.2
unnamed: D11.1 (K), R5.2
unnamed: D12.1 (K), R6.2
unnamed: C12.1, U3.5 (XTAL1/CLKIN), Y1.1
unnamed: C13.1, U3.4 (XTAL2), Y1.2

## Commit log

2026-04-09 initial commit after name change from LBEAST to HoloCade
    Made-with: Cursor
2026-04-09 Update holocade-logo.png
    Made-with: Cursor
2026-04-14 Move README and tooling into HoloCade package; fix paths for new layout
2026-04-14 Flatten repo to UPM package root; bump to v0.1.3
    - Move HoloCade package contents to repository root; remove Unity host project files
    - Update README install URLs (no ?path=), scripts, .gitignore
    - Align package.json and docs to 0.1.3
2026-04-14 Docs: update Contributing development workflow for UPM package
2026-04-14 chore: move KiCAD PCBs to HoloCade_PCBs repository
    - Remove FirmwareExamples/PCBs~ and PCBs.meta from package; link README to GitHub
    - Point FirmwareExamples README at HoloCade_PCBs
    - Clarify KiCAD meta suppressor comment
2026-04-14 chore: move batch/shell tooling into BuildTooling~ for UPM import
2026-04-14 Add arcade cabinet IO bridge and hide UDP transport UnityEvent serialization
    - Runtime/Cabinet: packet-based ArcadeCabinetBridge, IO config, presets, diagnostics
    - HoloCadeUDPTransport: code-only UnityEvent backing fields (no inspector wiring)
    - Bump package to 0.1.4
    Made-with: Cursor
2026-04-14 Add Cabinet NEXT_STEPS.md (SDK diagnostics and boot entry roadmap)
    Made-with: Cursor
2026-04-15 docs(AGENTS): acronym capitalization in class names (Code Style)
    Made-with: Cursor
2026-04-26 Implement Cube edit-mode rig workflow and monitor-driven setup.
    Add monitor spec/catalog assets, drop-in Cube base onboarding docs, and editor debug tooling for live oblique frustum visualization and safe edit-time rig rebuild behavior.
    Made-with: Cursor
2026-04-26 Add missing Unity meta files for Cube editor assets.
    Made-with: Cursor
2026-04-26 Fix Cube frustum debug overlay to use actual camera far clip.
    Remove debug depth capping from the colored frustum draw path so editor overlays stay aligned with real camera frustum behavior while moving side cameras.
    Made-with: Cursor
2026-04-29 Add Cube GameRoot generation and display dimension hooks
2026-05-03 Cube: passthrough sizing, display aspect API, procedural ceiling
    - Passthrough portal quads use backdrop width/height multipliers as minimum
    size, then expand to passthroughTextureAspectWidth:Height (default 16:9);
    side camera off-axis frustum stays on the physical inner opening only.
    - Default backdrop multipliers set to 6.125 (previous effective size with
    30% reduction folded in). Config adds texture aspect fields and ceiling
    hooks (ceilingMaterial, ceilingOffset).
2026-05-04 Cube README: pointer to dual 2.5GbE link assumptions in CubeModule spec
2026-05-04 Cube README: note OCuLink optional link upgrade in CubeModule spec
2026-05-04 Cube: HyperCube TCP/UDP bridge, SetPassthroughSources, pose channels
2026-05-04 HyperCube: HoloCadeUDPTransport listener mode, CubeBase wiring, remove duplicate UDP receiver
    - UDPTransportBase: bind listener, fix re-init shutdown; HoloCadeUDPTransport UdpRole LocalListener + TryGetFloat/TryGetInt32
    - HyperCubePoseTrackingProvider uses HoloCadeUDPTransport; drop HyperCubeUdpPoseReceiver
    - CubeBase prefab: TCP host, passthrough binder, UDP listener, pose provider
    - AGENTS: prefab/YAML guidance; CUBE_MODULE_README updated
2026-05-05 AGENTS: document default no-attribution commit policy
    Clarify that Cursor co-author trailers are opt-in, explain why --no-verify does not bypass prepare-commit-msg, and provide a safe one-off hooksPath method for message cleanup.
2026-05-05 README: add Cube omni arcade example and roadmap update
    Add the Omnidirectional Holographic Arcade example with HyperCube run guidance, and reorder roadmap milestones to mark v0.1.3 Cube baseline complete while advancing in-progress work to v0.1.4.
2026-05-08 Cube: display-mode aware rig, station-camera SDK contract, FPS HUD
    - CubeDisplayMode enum with SingleDisplay (editor / PC test build, all
    side cameras render to Display 1) and MultiDisplayCabinet (production
    cabinet build, each side camera pinned to its own physical display).
    - CubeRuntimeConfig: per-side display index fields (N/S/E/W) and
    activateExtraDisplaysInBuild flag; clamped + validated.
    - CubeRigController: ApplyTargetDisplaysToCameras called from
2026-05-10 feat(cube): OmniText TMP fan-out, prefab, station layers, tests
    - OmniTextElement: fixed per-side yaw, station layer assignment, no live camera billboard
    - CubeRuntimeConfig + CubeRigController: opponent OmniText layer culling
    - OmniText.prefab under CubeAssets; TMP/UGUI package + asmdef refs
    - Editor tests for station layers and element fan-out; README + AGENTS updates
2026-05-10 OmniText: fix prefab authoring, stray cleanup, never destroy NSEW shells
    - OmniTextElement: stop deleting/recreating authored OmniText_* children; remove wrong-pipeline Destroy path.
    - Edit-mode driveStationContentFromParentInEditMode (default off) so Prefab Apply is not overwritten by ExecuteAlways; slim OnValidate to defer Rebuild only.
    - Clear HideFlags on shells; SyncSide guards for prefab/cube-less contexts unchanged for creates-only-when-missing.
    - OmniTextElementEditor: stray/duplicate cleanup menus, Unity-suffix names, invalid-scene strays, unhide hierarchies.
    - OmniText.prefab + README: align docs with find-or-create station shells workflow.
2026-05-11 OmniTextElement updates, jumbotron prefab, and cube assets
    - OmniTextElement: FontSize and related behavior for HoloSnake lobby OmniText.
    - Add Jumbotron.prefab and PlayerNotificationStyle.asset under CubeAssets.
    - README updates.
2026-05-12 SDK: cabinet preset, CubeBase IO config, inspector purpose, public SDK docs
    AGENTS: one-way docs vs private title repos. README vendor-neutral cabinet bench notes.
    Rename CabinetConfigPresets to CreateReferenceFourPlayerCabinet; ship ArcadeCabinetIOConfig
    on [CubeBase] with ArcadeCabinetBridge. HoloCadeUDPTransport and cabinet/cube/hypercube
    tweaks. Add InspectorPurposeAttribute + drawer and CubeBase root inspectors.
2026-05-17 SDK: cabinet Free Play credit policy, roadmap v0.1.4–0.1.6, OmniText depth
    Add CabinetCreditEvaluation with freePlayEnabled on IO config and bridge accessor so titles share one paid vs Free Play claim path. Document v0.1.5 service menu and v0.1.6 biometric consent on the ro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

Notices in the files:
README.md:
📄 License:
This project is licensed under the **MIT License** - see the [LICENSE](LICENSE) file for details.
TL;DR:** Free to use, modify, and distribute for personal or commercial projects. Attribution appreciated but not required.
HoloCade is open-source under the MIT License. Got ideas for how to make HoloCade better? Contributions are welcome!
